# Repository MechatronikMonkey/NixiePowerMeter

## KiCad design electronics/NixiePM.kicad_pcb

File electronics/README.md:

# WB50 KiCad Projektstruktur

Dieses Verzeichnis enthält das komplette KiCad-Projekt inkl. lokaler Bibliotheken, Teilschaltpläne, PCB-Hilfsdateien und Fertigungs-/Montageordner.

## Struktur
- libraries/
  - symbols/: Projekt‑Symbolbibliothek `wb50_symbols.kicad_sym`
  - footprints/: Projekt‑Footprints in `wb50_footprints.pretty/`
  - 3dmodels/: 3D‑Modelle (optional)
- schematics/: Teilschaltpläne, die später als Hierarchieblätter in `wb50.kicad_sch` eingebunden werden
- pcb/: DXF‑Hilfsdateien (Board‑Outline, Keepouts, Front/Rear‑Panel‑Guides)
- fabrication/: Gerber/Bohrdaten, Fab‑Notizen, Stückliste und Pick&Place
- simulation/spice/: SPICE‑Testbench und Model‑Hinweise

## Erste Schritte (Front‑/Rear‑Panel zuerst)
1) Symbole & Footprints erstellen/zuweisen
   - Externe Bedienelemente (Potenziometer, Schalter, Klinken, Netz‑/Standby‑Schalter, LED) als Symbole in `wb50_symbols.kicad_sym` pflegen.
   - Passende Footprints in `wb50_footprints.pretty/` ablegen oder Standardbibliotheken verwenden.
2) Teilschaltpläne befüllen
   - In `schematics/` liegen Platzhalter für Preamp, Voicing‑Relays, Tone‑Stack, FX‑Loop, Masters, PI, Power‑Amp, NFB‑Shaping, Power‑Supply, Control‑Power.
   - Externe Bedienelemente zunächst sauber im Schaltplan anlegen (mit eindeutigen Referenzen und Netz‑Namen).
3) PCB‑Vormontage der Front/Rear‑Elemente
   - Im PCB‑Editor die Footprints der externen Bedienelemente zuerst entsprechend der Front/Rear‑Panel‑Mechanik platzieren.
   - DXF‑Hilfsgeometrie in `pcb/` importieren (Panel‑Bohrungen/Abstände), um Positionen zu verifizieren.
4) Verdrahtung/Netze nachziehen
   - Danach restliche Baugruppen platzieren, sensible Netze kurz halten (Grids, CF→Tonestack), sternförmige Masseführung beachten.

Tipp: In der `sym-lib-table` und `fp-lib-table` sind die lokalen Bibliotheken bereits auf `${KIPRJMOD}` referenziert.

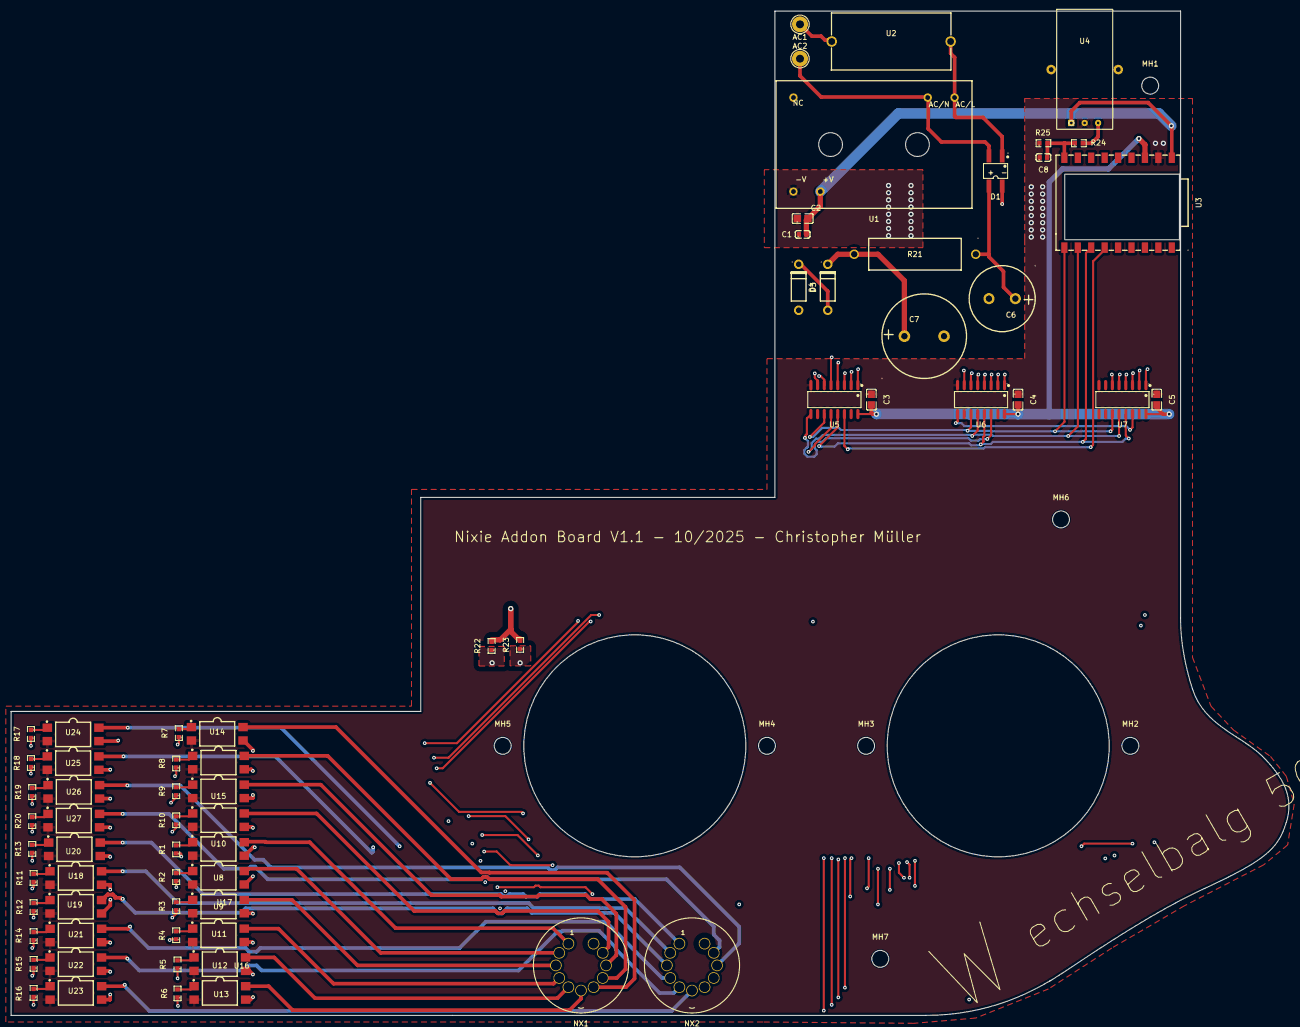
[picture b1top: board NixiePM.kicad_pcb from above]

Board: 4 copper layers, 241.7 x 190.0 mm, 74 parts (0 on the bottom side), 80 nets.

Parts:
AC1, AC2: AC ~ 230V; TestPoint_THTPad_D3.0mm_Drill1.5mm
C1: CL10A475KO8NNNC; C0603
C2, C3, C4, C5: 100nF 50V X7R; C0805
C6: 33uF 500V 5R5-ESR; CAP-TH_BD12.5-P5.00-D0.6-FD
C7: 450BXW47MEFR16X25; CAP-TH_BD16.0-P7.50-D1.2-FD
C8: 0603B472K500NT; C0603
D1: MB26S_C475740; MBS_L4.7-W4.0-P2.50-LS7.0-BL
D3, D4: 2EZ91D5; DO-41_BD2.4-L4.7-P8.70-D0.8-RD
MH1, MH2, MH3, MH4, MH5, MH6, MH7: MountHole; MountingHole_3.2mm_M3
NX1, NX2: IN-8; IN-8_NIXIE
R1, R2, R3, R4, R5, R6, R7, R8, R9, R10, R11, R12, R13, R14, R15, R16, R17, R18, R19, R20: 0603WAF2000T5E; R0603
R21: CFR03SJ0153AA0_15k; RES-TH_BD6.0-L17.5-P21.50-D0.8
R22, R23: 0603WAF1002T5E; R0603
R24: 0603WAF1201T5E; R0603
R25: 0603WAF3301T5E; R0603
U1: IRM-03-5; PWRM-TH_IRM-03-5-DIP5
U2: 16A 20mm 500V 5mm Plugin Fuse; FUSE-TH_L22.5-W10.8-P22.50_0031.8201.G
U3: ESP32-ZERO; COMM-SMD_ESP32-ZERO
U4: QNHC3; HALL-SENSOR_5P-P2.54-H13.5
U5, U6, U7: 74HC595D,118; SOIC-16_L9.9-W3.9-P1.27-LS6.0-BL
U8, U9, U10, U11, U12, U13, U14, U15, U16, U17, U18, U19, U20, U21, U22, U23, U24, U25, U26, U27: KAQY214ATLD; SMD-4_L4.6-W6.4-P2.54-LS10.0-BR

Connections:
+3V3: C3.2, C4.2, C5.2, U3.21 (3V3), U5.16 (VCC), U6.16 (VCC), U7.16 (VCC)
+5V: C1.2, C2.2, U1.16 (+VO), U3.23 (5V), U4.1 (5V)
+182V: C7.1, D3.1 (K), R21.2, R22.2, R23.2
+325V: C6.1, D1.3 (+), R21.1
/Anode1: NX1.11 (A), R22.1
/Anode2: NX2.11 (A), R23.1
/Clock: U3.9 (GP7), U5.11 (SHCP), U6.11 (SHCP), U7.11 (SHCP)
/Data: U3.6 (GP10), U5.14 (DS)
/Enable: U3.7 (GP9), U5.13 (OE#), U6.13 (OE#), U7.13 (OE#)
/Latch: U3.8 (GP8), U5.12 (STCP), U6.12 (STCP), U7.12 (STCP)
/NixieDigit1/Digital: R1.1, U5.1 (Q1)
/NixieDigit1/Nixie: NX1.1 (K1), U10.4 (S)
/NixieDigit2/Digital: R2.1, U5.2 (Q2)
/NixieDigit2/Nixie: NX1.2 (K2), U8.4 (S)
/NixieDigit3/Digital: R3.1, U5.3 (Q3)
/NixieDigit3/Nixie: NX1.3 (K3), U9.4 (S)
/NixieDigit4/Digital: R4.1, U5.4 (Q4)
/NixieDigit4/Nixie: NX1.4 (K4), U11.4 (S)
/NixieDigit5/Digital: R5.1, U5.5 (Q5)
/NixieDigit5/Nixie: NX1.5 (K5), U12.4 (S)
/NixieDigit6/Digital: R6.1, U5.6 (Q6)
/NixieDigit6/Nixie: NX1.6 (K6), U13.4 (S)
/NixieDigit7/Digital: R7.1, U5.7 (Q7)
/NixieDigit7/Nixie: NX1.7 (K7), U14.4 (S)
/NixieDigit8/Digital: R8.1, U6.1 (Q1)
/NixieDigit8/Nixie: NX1.8 (K8), U15.4 (S)
/NixieDigit9/Digital: R9.1, U6.2 (Q2)
/NixieDigit9/Nixie: NX1.9 (K9), U16.4 (S)
/NixieDigit10/Digital: R10.1, U6.3 (Q3)
/NixieDigit10/Nixie: NX1.10 (K0), U17.4 (S)
/NixieDigit11/Digital: R13.1, U6.4 (Q4)
/NixieDigit11/Nixie: NX2.1 (K1), U20.4 (S)
/NixieDigit12/Digital: R11.1, U6.5 (Q5)
/NixieDigit12/Nixie: NX2.2 (K2), U18.4 (S)
/NixieDigit13/Digital: R12.1, U6.6 (Q6)
/NixieDigit13/Nixie: NX2.3 (K3), U19.4 (S)
/NixieDigit14/Digital: R14.1, U6.7 (Q7)
/NixieDigit14/Nixie: NX2.4 (K4), U21.4 (S)
/NixieDigit15/Digital: R15.1, U7.1 (Q1)
/NixieDigit15/Nixie: NX2.5 (K5), U22.4 (S)
/NixieDigit16/Digital: R16.1, U7.2 (Q2)
/NixieDigit16/Nixie: NX2.6 (K6), U23.4 (S)
/NixieDigit17/Digital: R17.1, U7.3 (Q3)
/NixieDigit17/Nixie: NX2.7 (K7), U24.4 (S)
/NixieDigit18/Digital: R18.1, U7.4 (Q4)
/NixieDigit18/Nixie: NX2.8 (K8), U25.4 (S)
/NixieDigit19/Digital: R19.1, U7.5 (Q5)
/NixieDigit19/Nixie: NX2.9 (K9), U26.4 (S)
/NixieDigit20/Digital: R20.1, U7.6 (Q6)
/NixieDigit20/Nixie: NX2.10 (K0), U27.4 (S)
AC1: D1.1 (AC), U1.1 (AC/L), U2.2
AC2: AC2.1, D1.2 (AC), U1.3 (AC/N)
GND: C1.1, C2.1, C3.1, C4.1, C5.1, C8.1, R25.1, U1.14 (-VO), U3.22 (GND), U4.2 (GND), U5.8 (GND), U6.8 (GND), U7.8 (GND), U8.2 (K), U9.2 (K), U10.2 (K), U11.2 (K), U12.2 (K), U13.2 (K), U14.2 (K), U15.2 (K), U16.2 (K), U17.2 (K), U18.2 (K), U19.2 (K), U20.2 (K), U21.2 (K), U22.2 (K), U23.2 (K), U24.2 (K), U25.2 (K), U26.2 (K), U27.2 (K)
GND-HV: C6.2, C7.2, D1.4 (-), D4.2 (A), U8.3 (S1), U9.3 (S1), U10.3 (S1), U11.3 (S1), U12.3 (S1), U13.3 (S1), U14.3 (S1), U15.3 (S1), U16.3 (S1), U17.3 (S1), U18.3 (S1), U19.3 (S1), U20.3 (S1), U21.3 (S1), U22.3 (S1), U23.3 (S1), U24.3 (S1), U25.3 (S1), U26.3 (S1), U27.3 (S1)
unnamed: AC1.1, U2.1
unnamed: D3.2 (A), D4.1 (K)
unnamed: C8.2, R24.1, R25.2, U3.15 (GP6)
unnamed: R24.2, U4.3 (OUT)
unnamed: U5.9 (Q7S), U6.14 (DS)
unnamed: U6.9 (Q7S), U7.14 (DS)
unnamed: R2.2, U8.1 (A)
unnamed: R3.2, U9.1 (A)
unnamed: R1.2, U10.1 (A)
unnamed: R4.2, U11.1 (A)
unnamed: R5.2, U12.1 (A)
unnamed: R6.2, U13.1 (A)
unnamed: R7.2, U14.1 (A)
unnamed: R8.2, U15.1 (A)
unnamed: R9.2, U16.1 (A)
unnamed: R10.2, U17.1 (A)
unnamed: R11.2, U18.1 (A)
unnamed: R12.2, U19.1 (A)
unnamed: R13.2, U20.1 (A)
unnamed: R14.2, U21.1 (A)
unnamed: R15.2, U22.1 (A)
unnamed: R16.2, U23.1 (A)
unnamed: R17.2, U24.1 (A)
unnamed: R18.2, U25.1 (A)
unnamed: R19.2, U26.1 (A)
unnamed: R20.2, U27.1 (A)

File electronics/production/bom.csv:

Designator,Footprint,Quantity,Value,LCSC Part #
"AC1, AC2",TestPoint_THTPad_D3.0mm_Drill1.5mm,2,AC ~ 230V,
C1,C0603,1,CL10A475KO8NNNC,C19666
"C2, C3, C4, C5",C0805,4,100nF 50V X7R,C49678
C6,CAP-TH_BD12.5-P5.00-D0.6-FD,1,33uF 500V 5R5-ESR,C443401
C7,CAP-TH_BD16.0-P7.50-D1.2-FD,1,450BXW47MEFR16X25,C440818
C8,C0603,1,0603B472K500NT,C53987
D1,MBS_L4.7-W4.0-P2.50-LS7.0-BL,1,MB26S_C475740,C475740
"D3, D4",DO-41_BD2.4-L4.7-P8.70-D0.8-RD,2,2EZ91D5,C5464809
"MH1, MH2, MH3, MH4, MH5, MH6, MH7",MountingHole_3.2mm_M3,7,MountHole,
"NX1, NX2",IN-8_NIXIE,2,IN-8,
"R1, R10, R11, R12, R13, R14, R15, R16, R17, R18, R19, R2, R20, R3, R4, R5, R6, R7, R8, R9",R0603,20,0603WAF2000T5E,C8218
R21,RES-TH_BD6.0-L17.5-P21.50-D0.8,1,CFR03SJ0153AA0_15k,C2905221
"R22, R23",R0603,2,0603WAF1002T5E,C25804
R24,R0603,1,0603WAF1201T5E,C22765
R25,R0603,1,0603WAF3301T5E,C22978
U1,PWRM-TH_IRM-03-5-DIP5,1,IRM-03-5,C6969425
"U10, U11, U12, U13, U14, U15, U16, U17, U18, U19, U20, U21, U22, U23, U24, U25, U26, U27, U8, U9",SMD-4_L4.6-W6.4-P2.54-LS10.0-BR,20,KAQY214ATLD,C136448
U2,FUSE-TH_L22.5-W10.8-P22.50_0031.8201.G,1,16A 20mm 500V 5mm Plugin Fuse,C3204125
U3,COMM-SMD_ESP32-ZERO,1,ESP32-ZERO,C5350143
U4,HALL-SENSOR_5P-P2.54-H13.5,1,QNHC3,
"U5, U6, U7",SOIC-16_L9.9-W3.9-P1.27-LS6.0-BL,3,"74HC595D,118",C5947

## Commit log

2025-10-13 first schematic drawing
2025-10-13 schematic ready, layout started
2025-11-12 update resistor
2025-11-12 update resistor, update voltages
2026-01-16 update schmatic
2026-01-16 update documentation
2026-01-16 initial software
2026-01-21 fix: schematic mistakes corrected
2026-01-21 fix: update software to use MR and correct bitshifting
2026-01-21 update gitignore
2026-01-21 fix: select correct ADC channel
2026-01-21 fix: update pcb polygones
2026-01-22 fix: watt calculation wrong
2026-01-22 feature: nvm save to rom
2026-01-22 feature: zero point calibration
2026-01-26 fix: platform version problems with tasmota version. cannot be changed at the moment. needs investigation
